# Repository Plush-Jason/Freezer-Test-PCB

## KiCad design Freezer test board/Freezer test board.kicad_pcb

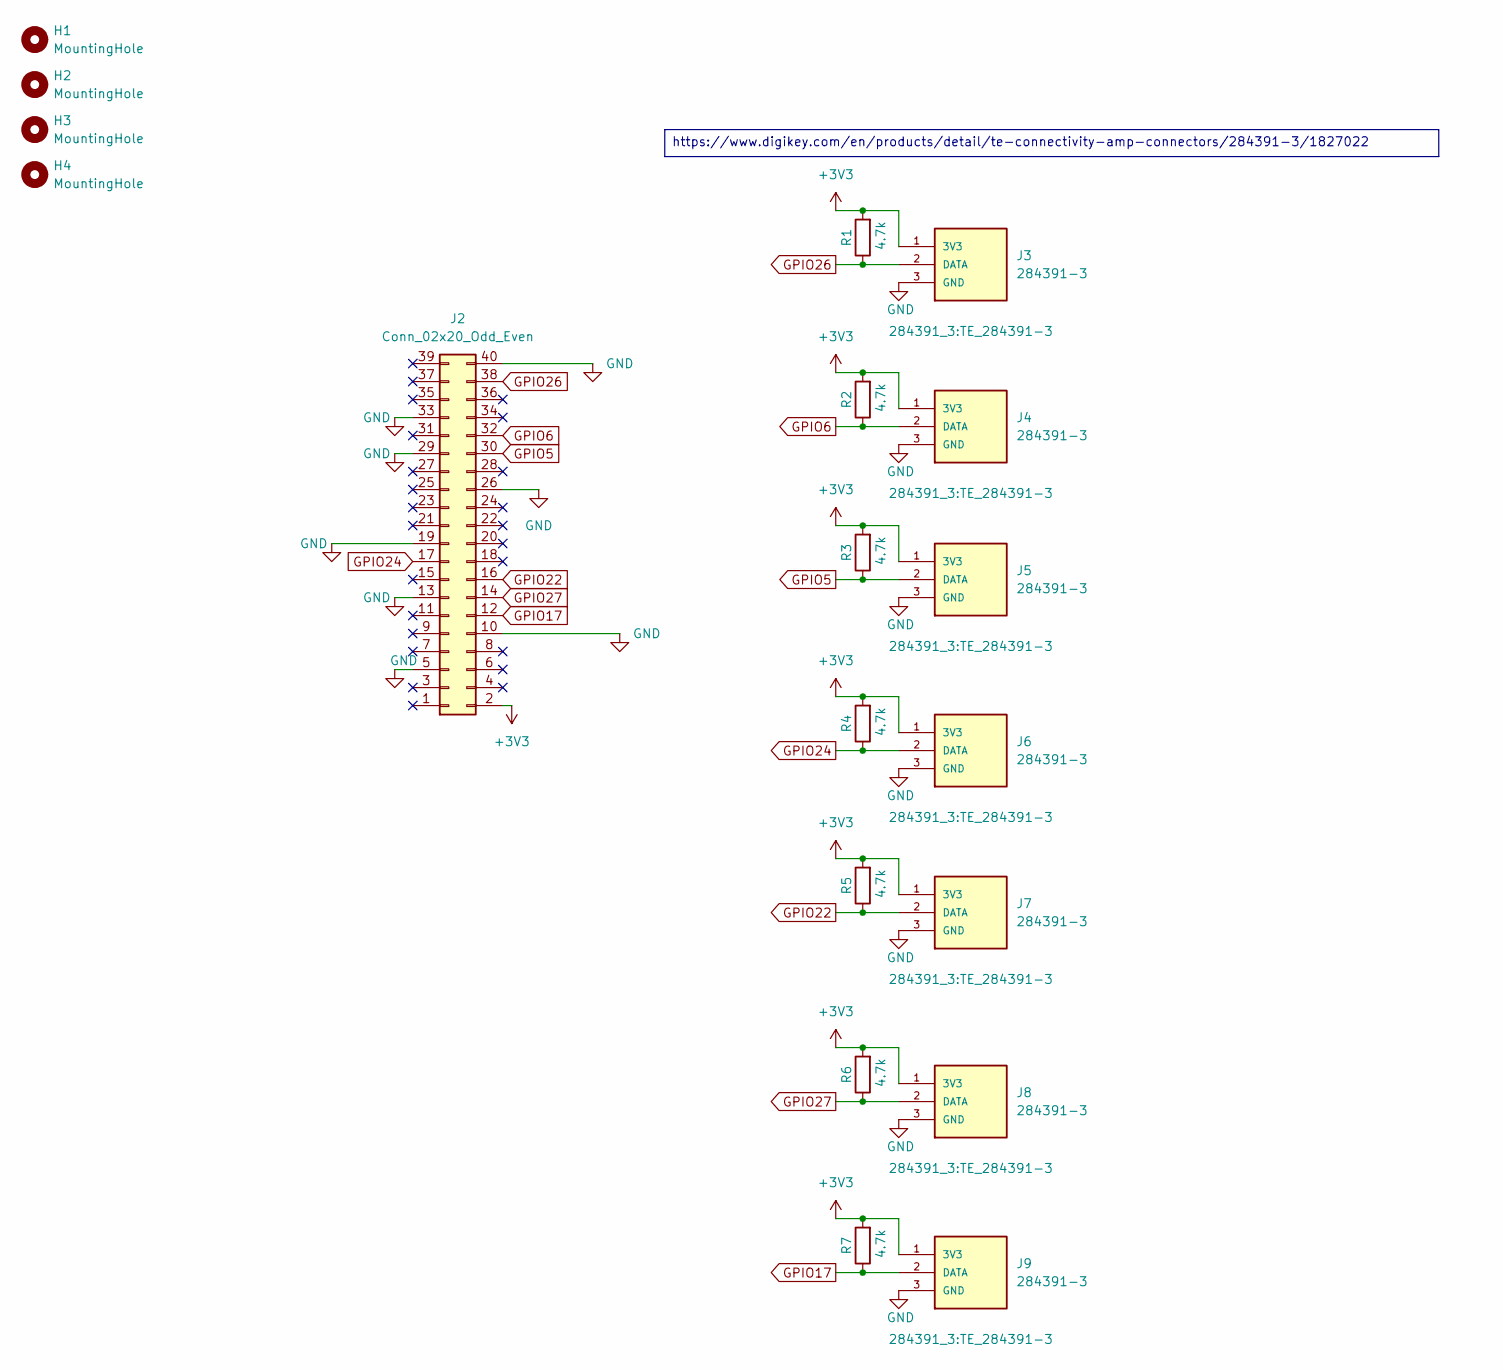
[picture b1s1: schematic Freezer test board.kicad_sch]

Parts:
H1, H2, H3, H4: MountingHole; MountingHole_2.7mm_M2.5_Pad
J2: Conn_02x20_Odd_Even; PinSocket_2x20_P2.54mm_Vertical
J3, J4, J5, J6, J7, J8, J9: 284391-3; TE_284391-3; PARTREV R
R1, R2, R3, R4, R5, R6, R7: 4.7k; R_Axial_DIN0207_L6.3mm_D2.5mm_P7.62mm_Horizontal

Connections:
+3V3: J2.2, J3.1 (3V3), J4.1 (3V3), J5.1 (3V3), J6.1 (3V3), J7.1 (3V3), J8.1 (3V3), J9.1 (3V3), R1.2, R2.2, R3.2, R4.2, R5.2, R6.2, R7.2
GND: J2.5, J2.10, J2.13, J2.19, J2.26, J2.29, J2.33, J2.40, J3.3 (GND), J4.3 (GND), J5.3 (GND), J6.3 (GND), J7.3 (GND), J8.3 (GND), J9.3 (GND)
GPIO5: J2.30, J5.2 (DATA), R3.1
GPIO6: J2.32, J4.2 (DATA), R2.1
GPIO17: J2.12, J9.2 (DATA), R7.1
GPIO22: J2.16, J7.2 (DATA), R5.1
GPIO24: J2.17, J6.2 (DATA), R4.1
GPIO26: J2.38, J3.2 (DATA), R1.1
GPIO27: J2.14, J8.2 (DATA), R6.1

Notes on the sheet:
https://www.digikey.com/en/products/detail/te-connectivity-amp-connectors/284391-3/1827022

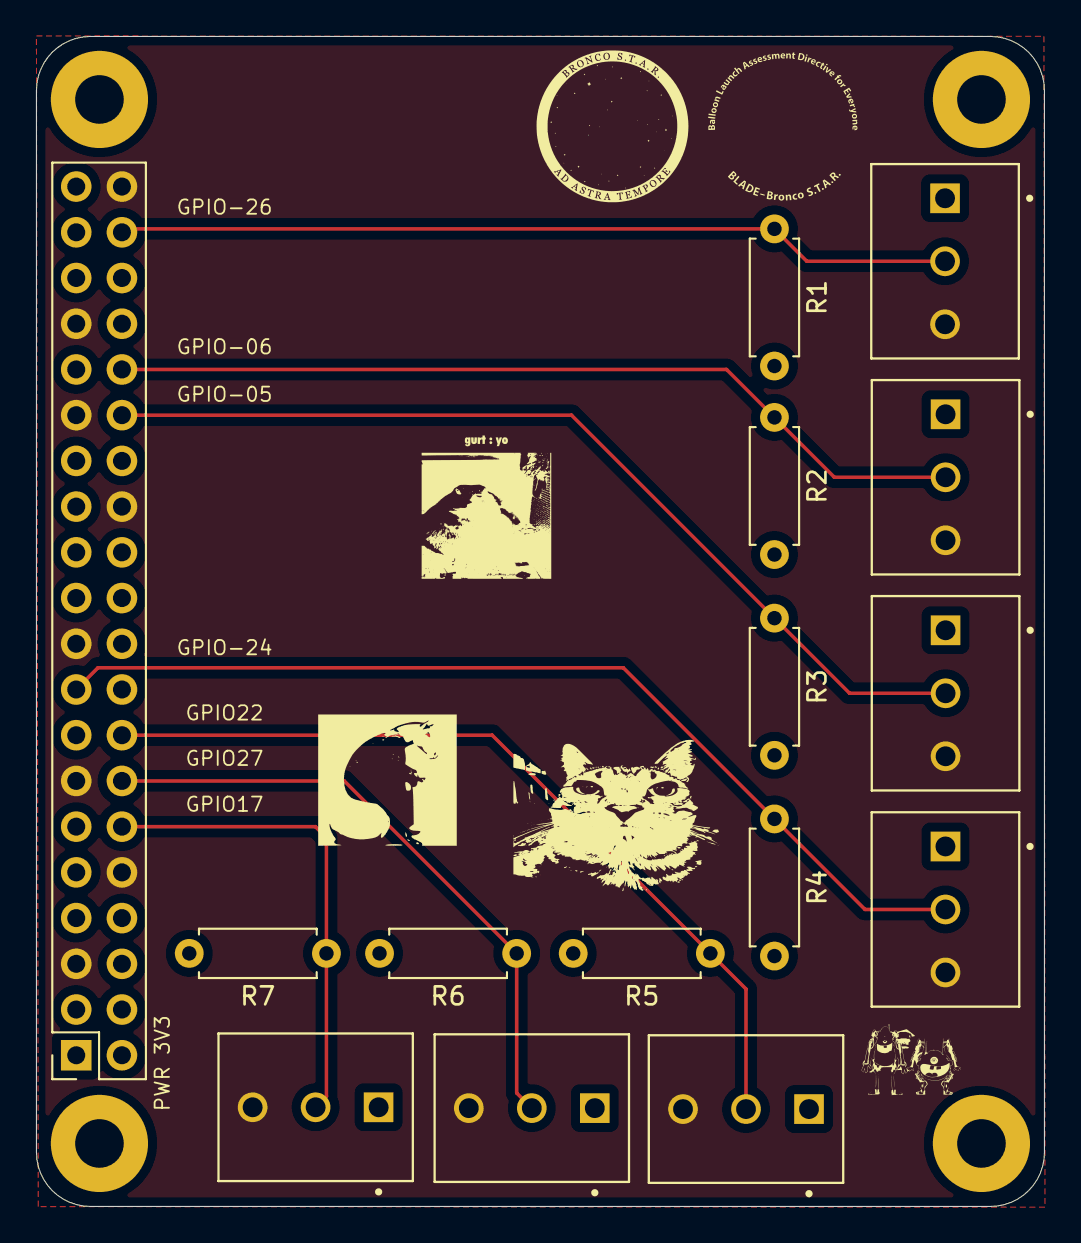
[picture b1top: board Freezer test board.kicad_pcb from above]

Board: 4 copper layers, 56.0 x 65.0 mm, 19 parts (0 on the bottom side), 9 nets.

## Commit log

2026-05-03 PCB(I think is done)
    I Routed the GPIO pins to each terminal block, routed the 3V3 to the terminal blocks, Made the spacing for the mounting holes, Finished the layers for the PCB and then made the connections
2026-05-04 temp commit
    I just curved the edges of the PCB and un-did all the connection
2026-05-04 Temporary Push
    At the moment the most recent changes Made are the following: board has been shrunk by moving the terminal blocks in-between the mounting holes, the terminal blocks have been changed from 5.08mm to 3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
2026-05-04 changes layouts
2026-05-05 Changed to 1 GPIO and cleaned up the connections
    All of the Signals connections have been changed to go to One GPIO pin per the request of the software person. connections were cleaned up because they were all over the place.
2026-05-05 Reroute GPIO traces on top layer
2026-05-05 Finished Product
    Its done, all connections are routed and essential memes have been added.
2026-05-05 Revert "Finished Product"
    This reverts commit 4c5b83d13ff1ed3163e33f6f8de5480cfa8905a7.
2026-05-05 fixed?
    reverted to the Tri's previous push and then re did the signal tracks, re organized the resistors and terminal blocks. Other than everything is the exact same
2026-05-06 Finial Touches
    put what specific resistors are being used in the comments. Made the finial touches and re traced the resistors and spaced them further from the terminal blocks
2026-05-06 irrelevant
    just an updated link
2026-05-06 Filled copper, adjust mask+silkscreens arts
2026-05-06 Adjust mounting hole footprint to 2.7mm M2.5
2026-05-06 Generate JLCPCB files
2026-05-06 Logo updates
2026-05-06 production files
2026-05-06 final production files v1.0
2026-05-14 V1.1
    Revised the pin out for the traces 10 times and got a second opinion. they are all connected properly. added more memes, adjusted the text indicating what pin is what, added text for the 3V3 pin, Ens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
2026-05-14 Gbr
    Gbr Files for the PCB
